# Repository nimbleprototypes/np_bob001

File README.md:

np_bob001
=========

Adaptador SOIC a DIP 8 pines

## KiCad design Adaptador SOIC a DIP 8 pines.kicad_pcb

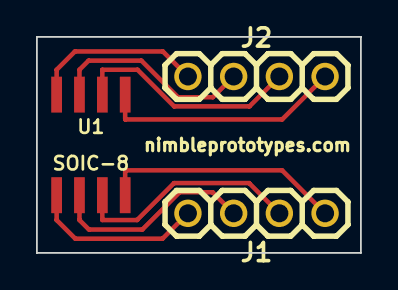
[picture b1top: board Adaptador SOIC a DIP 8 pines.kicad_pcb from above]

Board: 2 copper layers, 18.0 x 12.0 mm, 3 parts (0 on the bottom side), 8 nets.

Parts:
J1, J2: HEADER_4; header_4
U1: SOIC-8

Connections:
unnamed: J1.4, U1.1
unnamed: J2.2, U1.7
unnamed: J2.3, U1.6
unnamed: J2.4, U1.5
unnamed: J2.1, U1.8
unnamed: J1.3, U1.2
unnamed: J1.2, U1.3
unnamed: J1.1, U1.4

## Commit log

2014-03-22 Create Adaptador SOIC a DIP 8 pines
2014-03-22 Rename Adaptador SOIC a DIP 8 pines to Adaptador SOIC a DIP 8 pines.sch
